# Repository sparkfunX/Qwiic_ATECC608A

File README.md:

SparkFun Cryptographic Co-Processor Breakout - ATECC608A (Qwiic)
========================================

[*SparkFun Cryptographic Co-Processor Breakout - ATECC608A (Qwiic) (SPX-15838)*](https://www.sparkfun.com/products/15838)

The SparkX ATECC608A Cryptographic Co-processor Breakout allows you to add strong security to your IoT node, edge device, or embedded system. This includes <strong><u>a</u>symmetric</strong> authentication, <strong>symetric</strong> AES-128 encryption/decryption, and much more. Note, the ATECC608A has limited Arduino support and the complete datasheet is under NDA with Microchip.

This breakout board includes two Qwiic ports for plug and play functionality. Utilizing our handy Qwiic system, no soldering is required to connect it to the rest of your system. However, we still have broken out 0.1"-spaced pins in case you prefer to use a breadboard. The ATECC608A chip is capable of many cryptographic processes, including, but not limited to:

* Creating and securely storing unique asymmetric key pairs based on Elliptic Curve Cryptography (FIPS186-3).
* AES-128: Encrypt/Decrypt, Galois Field Multiply for GCM
* Creating and verifying 64-byte digital signatures (from 32-bytes of message data).
* Creating a shared secret key on a public channel via Elliptic Curve Diffie-Hellman Algorithm.
* SHA-256 & HMAC Hash including off-chip context save/restore
* Internal high quality FIPS random number generator. 

Repository Contents
-------------------

* **/Documentation** - Data sheets, additional product information
* **/Hardware** - Eagle design files (.brd, .sch)
* **/Production** - Production panel files (.brd)

Documentation
--------------
* [Schematic](https://cdn.sparkfun.com/assets/c/7/e/b/e/Qwiic_ATECC608A_SCHEMATIC.pdf)
* [Eagle Files](https://cdn.sparkfun.com/assets/1/9/5/f/5/Qwiic_ATECC608A.zip)
* [Board Dimensions](https://cdn.sparkfun.com/assets/7/7/3/9/5/Qwiic_ATECC608A_Dimensions.pdf)
* [Github Hardware Repo](https://github.com/sparkfunx/Qwiic_ATECC608A)
* [Datasheet Summary (ATECC608A)](https://cdn.sparkfun.com/assets/d/5/c/c/a/ATECC608A-CryptoAuthentication-Device-Summary-Data-Sheet-DS40001977B.pdf) Note, this is not the complete datasheet, which is under NDA with Microchip.
* [ArduinoECCX08 Arduino Library](https://github.com/arduino-libraries/ArduinoECCX08)
* [CryptoAuthLib - Microchip CryptoAuthentication Library (includes python support)](https://github.com/MicrochipTech/cryptoauthlib)
* [Microchip ATECC608A Product page](https://www.microchip.com/wwwproducts/en/ATECC608A)

License Information
-------------------

This product is _**open source**_! 

Please review the LICENSE.md file for license information. 

If you have any questions or concerns on licensing, please contact technical support on our [SparkFun forums](https://forum.sparkfun.com/viewforum.php?f=152).

Distributed as-is; no warranty is given.

- Your friends at SparkFun.

_<COLLABORATION CREDIT>_

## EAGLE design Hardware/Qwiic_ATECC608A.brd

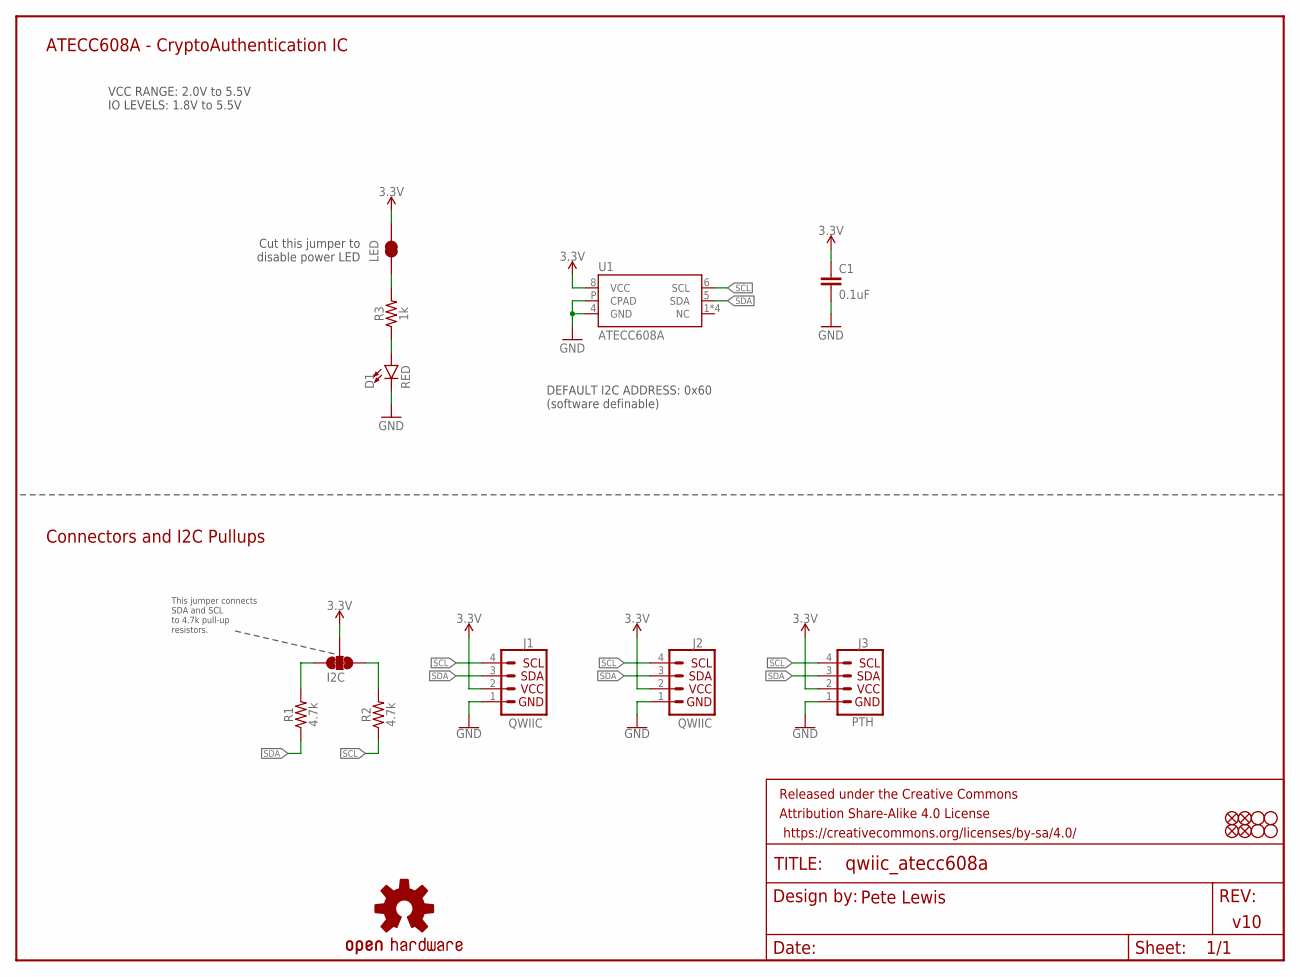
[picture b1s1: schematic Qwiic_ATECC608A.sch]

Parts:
C1: 0.1uF; 0603
D1: RED; LED-0603
FD1, FD2, FD3, FD4: FIDUCIAL1X2; FIDUCIAL-1X2
FRAME1: FRAME-LETTER; CREATIVE_COMMONS
H1, H2, H3, H4: STAND-OFF
I2C: JUMPER-SMT_3_2-NC_TRACE_SILK; SMT-JUMPER_3_2-NC_TRACE_SILK
J1, J2: QWIIC; JST04_1MM_RA
J3: PTH; 1X04_NO_SILK
LED: JUMPER-SMT_2_NC_TRACE_SILK; SMT-JUMPER_2_NC_TRACE_SILK
LOGO4: OSHW-LOGOS; OSHW-LOGO-S
R1, R2: 4.7k; 0603
R3: 1k; 0603
U1: ATECC608A; UDFN_2X3MM

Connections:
3.3V: C1.1, I2C.2, J1.2, J2.2, J3.2, LED.2, U1.8 (VCC)
GND: C1.2, D1.C, J1.1, J2.1, J3.1, U1.4 (GND), U1.P (CPAD)
unnamed: D1.A, R3.1
unnamed: I2C.3, R1.2
unnamed: I2C.1, R2.2
unnamed: LED.1, R3.2
SCL: J1.4, J2.4, J3.4, R2.1, U1.6 (SCL)
SDA: J1.3, J2.3, J3.3, R1.1, U1.5 (SDA)

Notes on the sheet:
This jumper connects SDA and SCL to 4.7k pull-up resistors.
v10
Pete Lewis
ATECC608A - CryptoAuthentication IC
VCC RANGE: 2.0V to 5.5V IO LEVELS: 1.8V to 5.5V
Connectors and I2C Pullups
Cut this jumper to disable power LED
DEFAULT I2C ADDRESS: 0x60 (software definable)

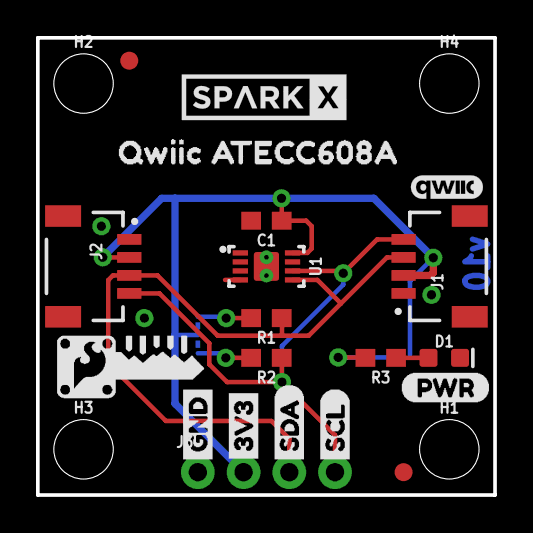
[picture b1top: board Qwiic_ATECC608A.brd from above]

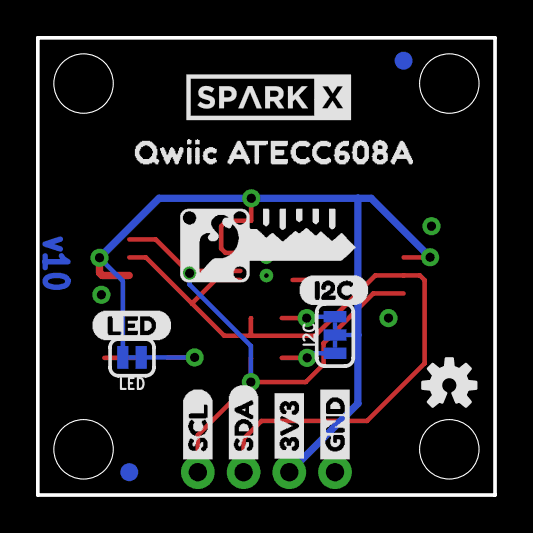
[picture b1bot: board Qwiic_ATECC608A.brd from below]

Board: 2 copper layers, 25.4 x 25.4 mm, 39 parts (14 on the bottom side), 8 nets.

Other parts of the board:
U$1: LED0
U$2, U$7: 3V34
U$3, U$5: SDA5
U$4, U$8: GND3
U$6, U$10: SCL6
U$9, U$19: SPARKX-MEDIUM
U$11, U$12: QWIIC_ATECC608A0
U$13: PWR0
U$15, U$18: CRYPTO_COPROCESSOR_LOGO#04#PNG
U$16: QWIIC_4MM
U$22: I2C0

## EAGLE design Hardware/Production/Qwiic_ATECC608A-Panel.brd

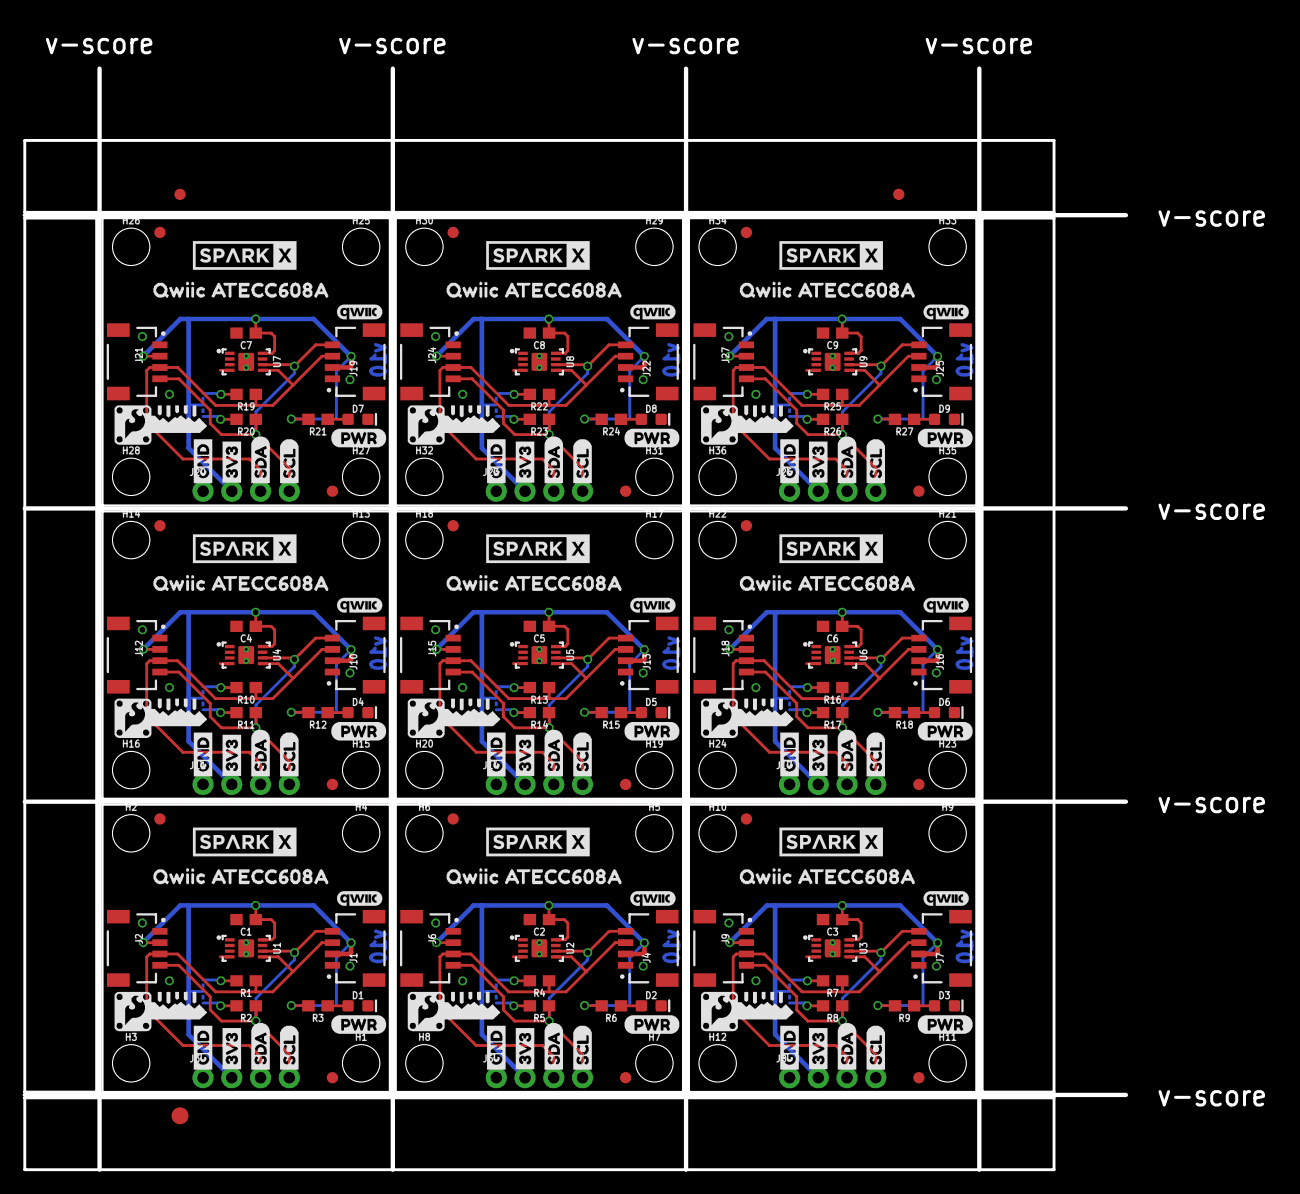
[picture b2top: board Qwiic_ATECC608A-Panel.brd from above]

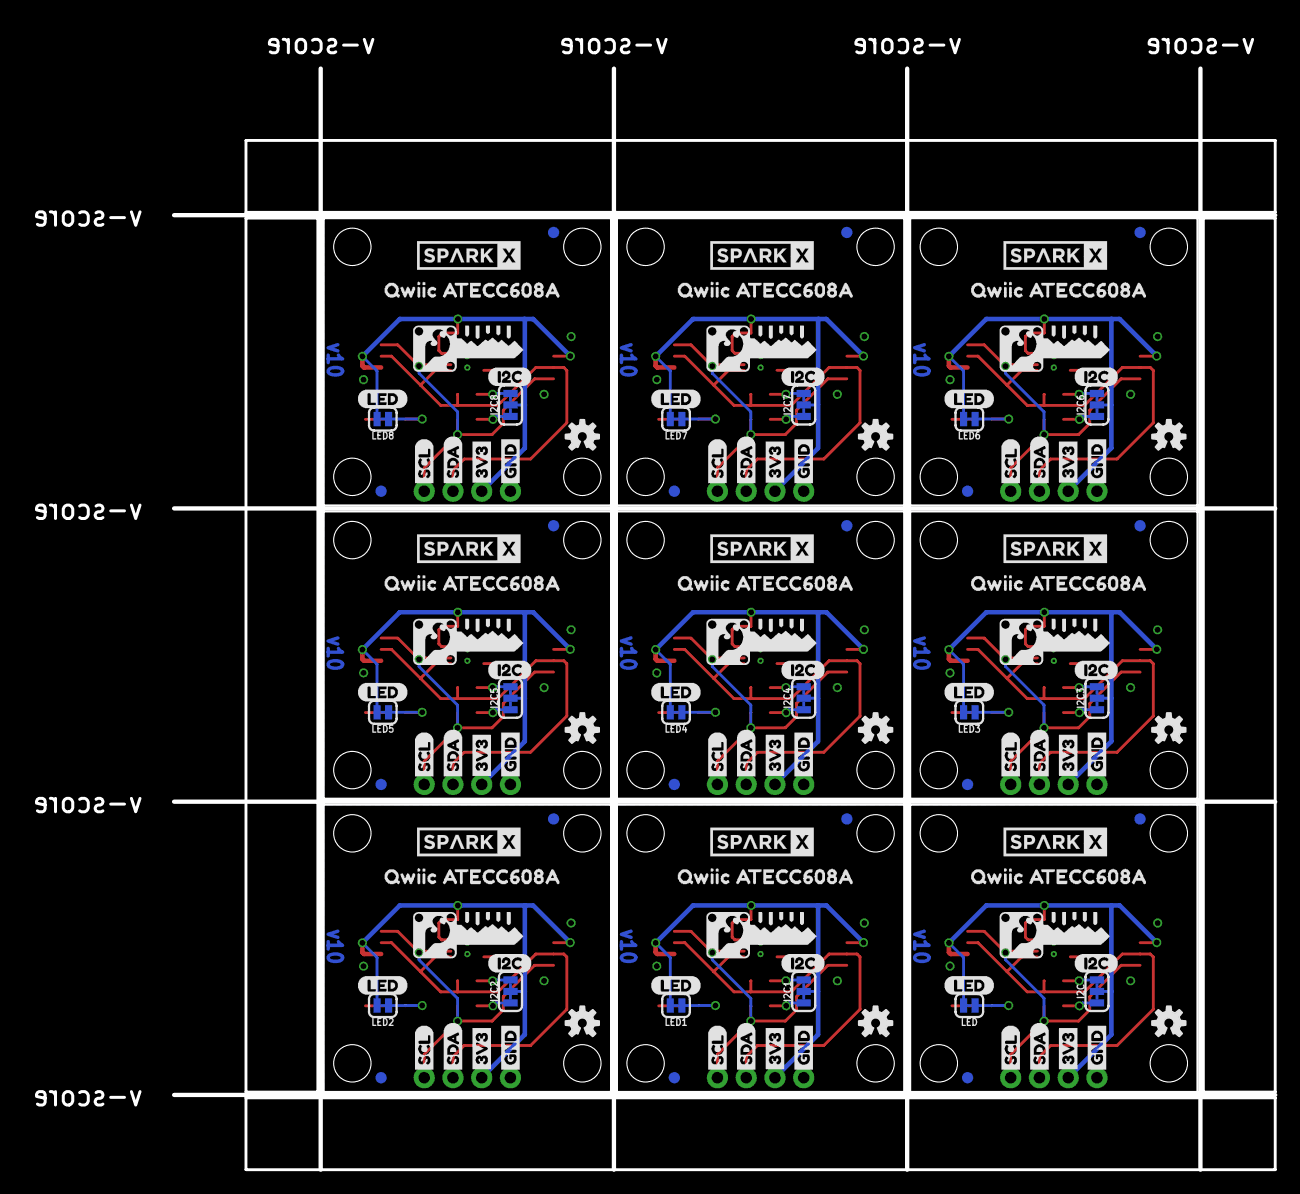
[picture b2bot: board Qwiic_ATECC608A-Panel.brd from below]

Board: 2 copper layers, 97.3 x 97.3 mm, 345 parts (126 on the bottom side), 72 nets.

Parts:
C1, C2, C3, C4, C5, C6, C7, C8, C9: 0.1uF; 0603
D1, D2, D3, D4, D5, D6, D7, D8, D9: RED; LED-0603
E$1, E$2: FIDUCIAL-1X2
E$3: FIDUCIAL-1.5X3
FD1, FD2, FD3, FD4, FD5, FD6, FD7, FD8, FD9, FD10, FD11, FD12, FD13, FD14, FD15, FD16, FD17, FD18, FD19, FD20, FD21, FD22, FD23, FD24, FD25, FD26, FD27, FD28, FD29, FD30, FD31, FD32, FD33, FD34, FD35, FD36: FIDUCIAL1X2; FIDUCIAL-1X2
H1, H2, H3, H4, H5, H6, H7, H8, H9, H10, H11, H12, H13, H14, H15, H16, H17, H18, H19, H20, H21, H22, H23, H24, H25, H26, H27, H28, H29, H30, H31, H32, H33, H34, H35, H36: STAND-OFF
I2C, I2C1, I2C2, I2C3, I2C4, I2C5, I2C6, I2C7, I2C8: SMT-JUMPER_3_2-NC_TRACE_SILK
J1, J2, J4, J6, J7, J9, J10, J12, J13, J15, J16, J18, J19, J21, J22, J24, J25, J27: QWIIC; JST04_1MM_RA
J3, J5, J8, J11, J14, J17, J20, J23, J26: PTH; 1X04_NO_SILK
LED, LED1, LED2, LED3, LED4, LED5, LED6, LED7, LED8: SMT-JUMPER_2_NC_TRACE_SILK
LOGO1, LOGO2, LOGO3, LOGO4, LOGO5, LOGO6, LOGO7, LOGO8, LOGO9: OSHW-LOGOS; OSHW-LOGO-S
R1, R2, R4, R5, R7, R8, R10, R11, R13, R14, R16, R17, R19, R20, R22, R23, R25, R26: 4.7k; 0603
R3, R6, R9, R12, R15, R18, R21, R24, R27: 1k; 0603
U1, U2, U3, U4, U5, U6, U7, U8, U9: ATECC608A; UDFN_2X3MM
U$1, U$28, U$46, U$64, U$82, U$100, U$118, U$136, U$154: LED0
U$2, U$7, U$21, U$26, U$40, U$44, U$58, U$62, U$76, U$80, U$94, U$98, U$112, U$116, U$130, U$134, U$148, U$152: 3V34
U$3, U$5, U$24, U$29, U$42, U$47, U$60, U$65, U$78, U$83, U$96, U$101, U$114, U$119, U$132, U$137, U$150, U$155: SDA5
U$4, U$8, U$23, U$27, U$41, U$45, U$59, U$63, U$77, U$81, U$95, U$99, U$113, U$117, U$131, U$135, U$149, U$153: GND3
U$6, U$10, U$25, U$30, U$43, U$48, U$61, U$66, U$79, U$84, U$97, U$102, U$115, U$120, U$133, U$138, U$151, U$156: SCL6
U$9, U$19, U$33, U$34, U$51, U$52, U$69, U$70, U$87, U$88, U$105, U$106, U$123, U$124, U$141, U$142, U$159, U$160: SPARKX-MEDIUM
U$11, U$12, U$35, U$36, U$53, U$54, U$71, U$72, U$89, U$90, U$107, U$108, U$125, U$126, U$143, U$144, U$161, U$162: QWIIC_ATECC608A0
U$13, U$17, U$38, U$56, U$74, U$92, U$110, U$128, U$146: PWR0
U$14, U$16, U$37, U$55, U$73, U$91, U$109, U$127, U$145: QWIIC_4MM
U$15, U$18, U$31, U$32, U$49, U$50, U$67, U$68, U$85, U$86, U$103, U$104, U$121, U$122, U$139, U$140, U$157, U$158: CRYPTO_COPROCESSOR_LOGO#04#PNG
U$20, U$22, U$39, U$57, U$75, U$93, U$111, U$129, U$147: I2C0

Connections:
3.3V: C1.1, I2C.2, J1.2, J2.2, J3.2, LED.2, U1.8
3.3V1: C2.1, I2C1.2, J4.2, J5.2, J6.2, LED1.2, U2.8
3.3V2: C3.1, I2C2.2, J7.2, J8.2, J9.2, LED2.2, U3.8
3.3V3: C4.1, I2C3.2, J10.2, J11.2, J12.2, LED3.2, U4.8
3.3V4: C5.1, I2C4.2, J13.2, J14.2, J15.2, LED4.2, U5.8
3.3V5: C6.1, I2C5.2, J16.2, J17.2, J18.2, LED5.2, U6.8
3.3V6: C7.1, I2C6.2, J19.2, J20.2, J21.2, LED6.2, U7.8
3.3V7: C8.1, I2C7.2, J22.2, J23.2, J24.2, LED7.2, U8.8
3.3V8: C9.1, I2C8.2, J25.2, J26.2, J27.2, LED8.2, U9.8
GND: C1.2, D1.C, J1.1, J2.1, J3.1, U1.4, U1.P
GND1: C2.2, D2.C, J4.1, J5.1, J6.1, U2.4, U2.P
GND2: C3.2, D3.C, J7.1, J8.1, J9.1, U3.4, U3.P
GND3: C4.2, D4.C, J10.1, J11.1, J12.1, U4.4, U4.P
GND4: C5.2, D5.C, J13.1, J14.1, J15.1, U5.4, U5.P
GND5: C6.2, D6.C, J16.1, J17.1, J18.1, U6.4, U6.P
GND6: C7.2, D7.C, J19.1, J20.1, J21.1, U7.4, U7.P
GND7: C8.2, D8.C, J22.1, J23.1, J24.1, U8.4, U8.P
GND8: C9.2, D9.C, J25.1, J26.1, J27.1, U9.4, U9.P
unnamed: I2C1.3, R4.2
unnamed: I2C1.1, R5.2
unnamed: D1.A, R3.1
unnamed: I2C.3, R1.2
unnamed: I2C.1, R2.2
unnamed: D2.A, R6.1
unnamed: LED.1, R3.2
unnamed: LED1.1, R6.2
unnamed: I2C2.3, R7.2
unnamed: I2C2.1, R8.2
unnamed: D3.A, R9.1
unnamed: LED2.1, R9.2
unnamed: I2C3.3, R10.2
unnamed: I2C3.1, R11.2
unnamed: D4.A, R12.1
unnamed: LED3.1, R12.2
unnamed: I2C4.3, R13.2
unnamed: I2C4.1, R14.2
unnamed: D5.A, R15.1
unnamed: LED4.1, R15.2
unnamed: I2C5.3, R16.2
unnamed: I2C5.1, R17.2
unnamed: D6.A, R18.1
unnamed: LED5.1, R18.2
unnamed: I2C6.3, R19.2
unnamed: I2C6.1, R20.2
unnamed: D7.A, R21.1
unnamed: LED6.1, R21.2
unnamed: I2C7.3, R22.2
unnamed: I2C7.1, R23.2
unnamed: D8.A, R24.1
unnamed: LED7.1, R24.2
unnamed: I2C8.3, R25.2
unnamed: I2C8.1, R26.2
unnamed: D9.A, R27.1
unnamed: LED8.1, R27.2
SCL: J1.4, J2.4, J3.4, R2.1, U1.6
SCL1: J4.4, J5.4, J6.4, R5.1, U2.6
SCL2: J7.4, J8.4, J9.4, R8.1, U3.6
SCL3: J10.4, J11.4, J12.4, R11.1, U4.6
SCL4: J13.4, J14.4, J15.4, R14.1, U5.6
SCL5: J16.4, J17.4, J18.4, R17.1, U6.6
SCL6: J19.4, J20.4, J21.4, R20.1, U7.6
SCL7: J22.4, J23.4, J24.4, R23.1, U8.6
SCL8: J25.4, J26.4, J27.4, R26.1, U9.6
SDA: J1.3, J2.3, J3.3, R1.1, U1.5
SDA1: J4.3, J5.3, J6.3, R4.1, U2.5
SDA2: J7.3, J8.3, J9.3, R7.1, U3.5
SDA3: J10.3, J11.3, J12.3, R10.1, U4.5
SDA4: J13.3, J14.3, J15.3, R13.1, U5.5
SDA5: J16.3, J17.3, J18.3, R16.1, U6.5
SDA6: J19.3, J20.3, J21.3, R19.1, U7.5
SDA7: J22.3, J23.3, J24.3, R22.1, U8.5
SDA8: J25.3, J26.3, J27.3, R25.1, U9.5

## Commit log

2019-11-06 Initial SparkX commit

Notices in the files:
parts and their libraries:
SparkFun-Aesthetics: Licensing: Creative Commons ShareAlike 4.0 International - https://creativecommons.org/licenses/by-sa/4.0
SparkFun-Aesthetics: Released under the Creative Commons Attribution Share-Alike 4.0 License
SparkFun-Aesthetics: https://creativecommons.org/licenses/by-sa/4.0
